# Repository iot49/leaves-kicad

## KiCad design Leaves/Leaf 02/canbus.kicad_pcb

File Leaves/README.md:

# Leaves

## Leaf 01: FRAM, Gyro, Canbus, BMI270, Hall Current Sensors (ADS1015), Supply Voltage Sense

* FRAM
* Canbus
* INA3221     
  * BUG: IN1-, IN2- not connected - Vsense1, Vsense2 always zero
  * Channel3 works (Vbus = Vin = ~12V nominal)
* ADS1015
* BMI270
* TMP1075     
  * BUG: address conflict with ADS1015 (TMP1075 removed)

## Leaf 02: FRAM, Gyro, Canbus, BMI270, Hall Current Sensors (ADS1015), Voltage Sense, Temperature

* Leaf 01 fixed
  * TMP1075 at 0x49
  * INA3221: IN1-=IN1+, IN2-=IN2+

## Leaf 03: Hall Current Sensors (ADS1015), Voltage Sense, Temperature, Buses (???)

* Leaf 01/02 with different buses
  * no Canbus, Gyro

* 3 (or 4) Hall Current Sensors
* Switched 12V (2 simultaneously should suffice)
  * Fan
  * Battery low voltage disconnect Victron BP12/24-100
  * House to Chassis charger
* 3 voltage inputs
  * Ignition
  * Chassis battery voltage
  * BP12 disconnect. Note: Power Leaf from an unswitched source, e.g. chassis

Connectors:  (Hammond 1593VBK accommodates up to 93mm)
* 4 Hall         40   mm
* 1 fan          10   mm
* Tool free: 8   33   mm  (3.5mm, 16-24 gauge)
  * 2 for Power, Ground
  * 3 Voltage inputs
  * 2 Switched outputs (1 shared with fan?)
  * 1 extra?
* Extra grove connectors other side? 3/5V?
* Buses fro Trume, Xantrex, RVC, Linbus?

Maybe:

* Bus for
  * Truma water heater
  * Xantex freedom 2000
  * Dometic fridge (Linbus)

## Leaf 04: Cooling Fan Controller, 12V switched out

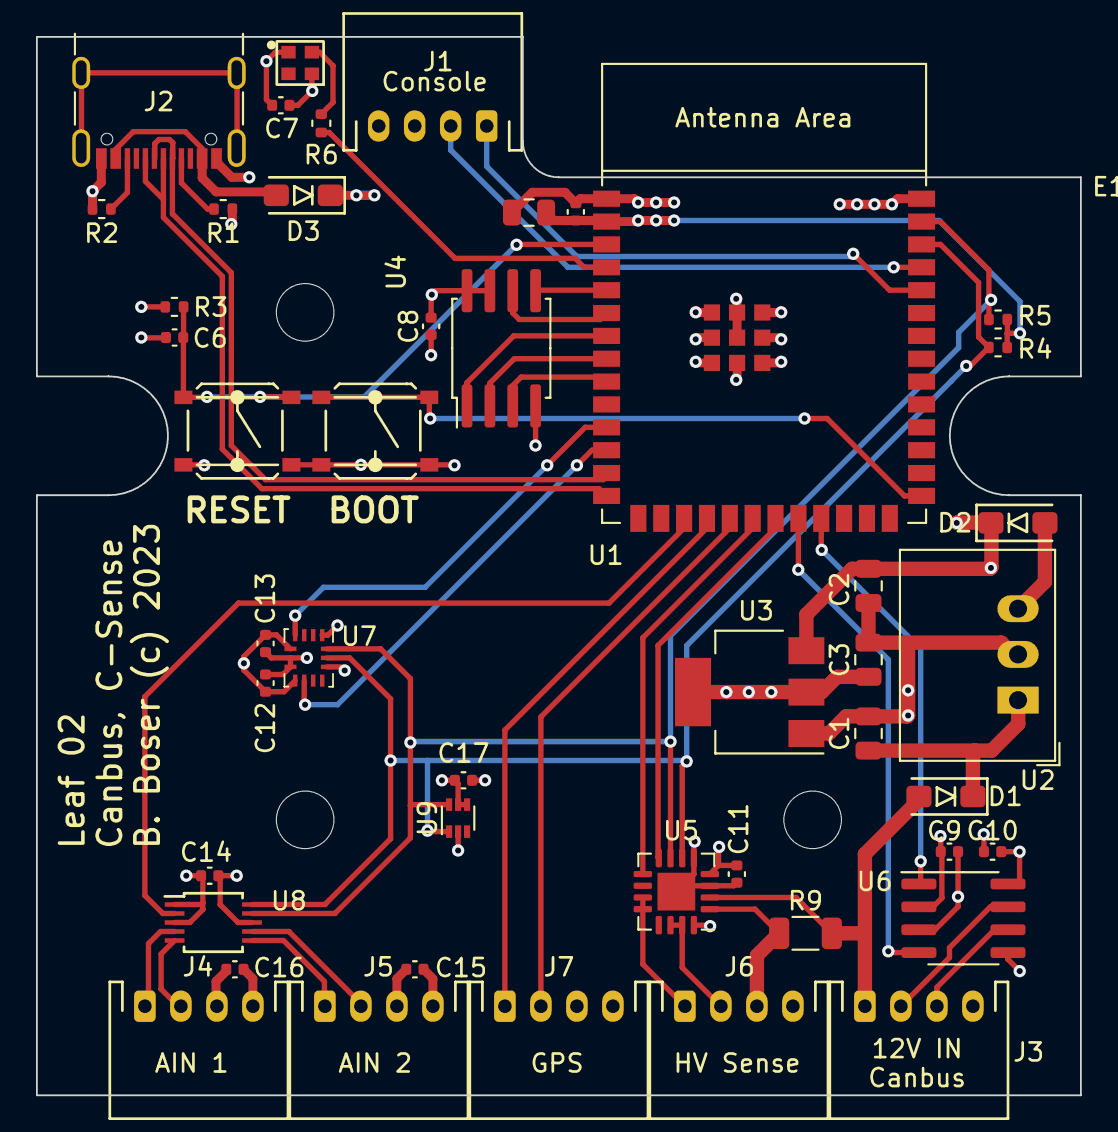
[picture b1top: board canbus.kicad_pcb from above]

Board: 4 copper layers, 58.0 x 58.8 mm, 47 parts (0 on the bottom side), 42 nets.

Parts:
C1, C2, C3, C4: 10u; C_0805_2012Metric
C5, C7, C8, C9, C10, C11, C12, C13, C14, C15, C16, C17: 100n; C_0402_1005Metric
C6: 1uF; C_0402_1005Metric
D1, D2, D3: 1N5819WS; SOD-123
E1: 1593k; Hammond_1593K_WROOM
J1: Console; JST_PH_S4B-PH-K_1x04_P2.00mm_Horizontal
J2: USB_C_Receptacle_USB2.0; USB_C_Receptacle_GCT_USB4105-xx-A_16P_TopMnt_Horizontal
J3: Power; JST_PH_S4B-PH-K_1x04_P2.00mm_Horizontal
J4: AIN1; JST_PH_S4B-PH-K_1x04_P2.00mm_Horizontal
J5: AIN2; JST_PH_S4B-PH-K_1x04_P2.00mm_Horizontal
J6: HV Sense; JST_PH_S4B-PH-K_1x04_P2.00mm_Horizontal
J7: GPS; JST_PH_S4B-PH-K_1x04_P2.00mm_Horizontal
LED1: SK6805; SK6805-EK20
R1, R2, R4, R5: 5.1k; R_0402_1005Metric
R3: 10k; R_0402_1005Metric
R6: 510; R_0402_1005Metric
R9: 150m; R_1206_3216Metric
SW1: BOOT; TS-1187A
SW2: RESET; TS-1187A
U1: ESP32-S3-WROOM-1
U2: R-78E5.0-1.0; Converter_DCDC_RECOM_R-78E-0.5_THT
U3: AMS1117-3.3; SOT-223-3_TabPin2
U4: MB85RS2MT; SOP-8_MP85RS2
U5: INA3221; Texas_RGV_S-PVQFN-N16_EP2.1x2.1mm
U6: MCP2562-E-SN; SOIC-8_3.9x4.9mm_P1.27mm
U7: BMI270; Bosch_LGA-14_3x2.5mm_P0.5mm
U8: ADS1015IDGS; TSSOP-10_3x3mm_P0.5mm
U9: TMP1075NDRLR; SOT-563

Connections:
+3.3V: C3.1, C4.1, C5.1, C7.1, C8.1, C10.1, C11.1, C12.1, C13.1, C14.1, C17.1, J7.3, LED1.4 (VDD), R3.1, R4.1, R5.2, U1.2 (3V3), U3.2 (VO), U4.7 (~HOLD), U4.8 (VDD), U5.4 (VS), U5.16 (VPU), U6.5 (Vio), U7.5 (VDDIO), U7.8 (VDD), U7.12 (CSB), U8.8 (VDD), U9.4 (A0), U9.5 (V+)
+5V: C2.1, C9.1, C15.1, C16.1, D2.1 (K), D3.1 (K), J1.3, J4.3, J5.3, U3.3 (VI), U6.3 (VDD)
+12V: C1.1, D1.1 (K), U2.1 (IN)
/VUSB: D3.2 (A), J2.A4 (VBUS), J2.A9 (VBUS), J2.B4 (VBUS), J2.B9 (VBUS)
/Vreg: D2.2 (A), U2.3 (OUT)
/io/AIN1+: J4.1, U8.4 (AIN0)
/io/AIN1-: J4.2, U8.5 (AIN1)
/io/AIN2+: J5.1, U8.6 (AIN2)
/io/AIN2-: J5.2, U8.7 (AIN3)
/io/CAN_H: J3.2, U6.7 (CANH)
/io/CAN_L: J3.3, U6.6 (CANL)
/io/Vout: J6.3, R9.1, U5.1 (IN-3)
/io/Vsense1: J6.1, U5.11 (IN-1), U5.12 (IN+1)
/io/Vsense2: J6.2, U5.14 (IN-2), U5.15 (IN+2)
ADC_ALERT: U1.17 (GPIO9/TOUCH9/ADC1_CH8/FSPIHD/SUBSPIHD), U8.2 (ALERT/RDY)
BOOT: SW1.1, U1.27 (GPIO0/BOOT)
CAN_RXD: U1.22 (GPIO14/TOUCH14/ADC2_CH3/FSPIWP/FSPIDQS/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), U6.4 (RXD)
CAN_TXD: U1.23 (GPIO21), U6.1 (TXD)
CS_CRITICAL: U1.20 (GPIO12/TOUCH12/ADC2_CH1/FSPICLK/FSPIIO6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), U5.9 (CRITICAL)
CS_WARNING: U1.21 (GPIO13/TOUCH13/ADC2_CH2/FSPIQ/FSPIIO7/S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), U5.8 (WARNING)
D+: J2.A6 (D+), J2.B6 (D+), U1.14 (GPIO20/U1CTS/ADC2_CH9/CLK_OUT1/USB_D+)
D-: J2.A7 (D-), J2.B7 (D-), U1.13 (GPIO19/U1RTS/ADC2_CH8/CLK_OUT2/USB_D-)
FRAM_CS: U1.7 (GPIO7/TOUCH7/ADC1_CH6), U4.1 (~CS)
FRAM_MISO: U1.8 (GPIO15/U0RTS/ADC2_CH4/XTAL_32K_P), U4.2 (SO)
FRAM_MOSI: U1.5 (GPIO5/TOUCH5/ADC1_CH4), U4.5 (SI)
FRAM_SCK: U1.6 (GPIO6/TOUCH6/ADC1_CH5), U4.6 (SCK)
FRAM_WP: U1.9 (GPIO16/U0CTS/ADC2_CH5/XTAL_32K_N), U4.3 (~WP)
GND: C1.2, C2.2, C3.2, C4.2, C5.2, C6.2, C7.2, C8.2, C9.2, C10.2, C11.2, C12.2, C13.2, C14.2, C15.2, C16.2, C17.2, J1.4, J2.A1 (GND), J2.A12 (GND), J2.B1 (GND), J2.B12 (GND), J3.4, J4.4, J5.4, J6.4, J7.4, LED1.2 (VSS), R1.2, R2.2, SW1.2, SW2.2, U1.1 (GND), U1.40 (GND), U1.41 (GND), U2.2 (GND), U3.1 (GND), U4.4 (GND), U5.3 (GND), U5.5 (A0), U5.17 (EP), U6.2 (VSS), U6.8 (STBY), U7.1 (SDO), U7.6 (GNDIO), U7.7 (GND), U8.1 (ADDR), U8.3 (GND), U9.2 (GND)
GPS_RX: J7.1, U1.18 (GPIO10/TOUCH10/ADC1_CH9/FSPICS0/FSPIIO4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)
GPS_TX: J7.2, U1.19 (GPIO11/TOUCH11/ADC2_CH0/FSPID/FSPIIO5/S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)
IMU_INT1: U1.11 (GPIO18/U1RXD/ADC2_CH7/CLK_OUT3), U7.4 (INT1)
IMU_INT2: U1.12 (GPIO8/TOUCH8/ADC1_CH7/SUBSPICS1), U7.9 (INT2)
LED: R6.1, U1.4 (GPIO4/TOUCH4/ADC1_CH3)
unnamed: J2.A5 (CC1), R1.1
unnamed: J2.B5 (CC2), R2.1
unnamed: LED1.3 (DIN), R6.2
RESET: C6.1, R3.2, SW2.1, U1.3 (EN)
SCL: R4.2, U1.38 (GPIO2/TOUCH2/ADC1_CH1), U5.6 (SCL), U7.13 (SCx), U8.10 (SCL), U9.1 (SCL)
SDA: R5.1, U1.39 (GPIO1/TOUCH1/ADC1_CH0), U5.7 (SDA), U7.14 (SDx), U8.9 (SDA), U9.6 (SDA)
U0RXD: J1.1, U1.36 (U0RXD/GPIO44/CLK_OUT2)
U0TXD: J1.2, U1.37 (U0TXD/GPIO43/CLK_OUT1)
Vin: D1.2 (A), J3.1, R9.2, U5.2 (IN+3)

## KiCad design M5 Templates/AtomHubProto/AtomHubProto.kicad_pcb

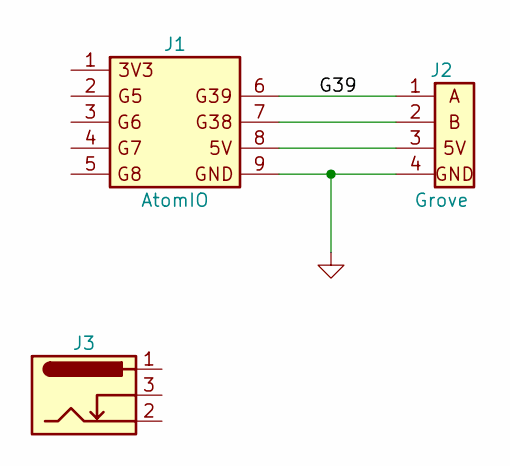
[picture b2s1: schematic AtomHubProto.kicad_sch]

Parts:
J1: AtomIO
J2: Grove
J3: Barrel_Jack_Switch; PowerJack

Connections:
/G39: J1.6, J2.1
GND: J1.9, J2.4 (GND)
unnamed: J1.7, J2.2
unnamed: J1.8, J2.3 (5V)

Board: 2 copper layers, 3 parts (0 on the bottom side), 4 nets, no tracks yet.

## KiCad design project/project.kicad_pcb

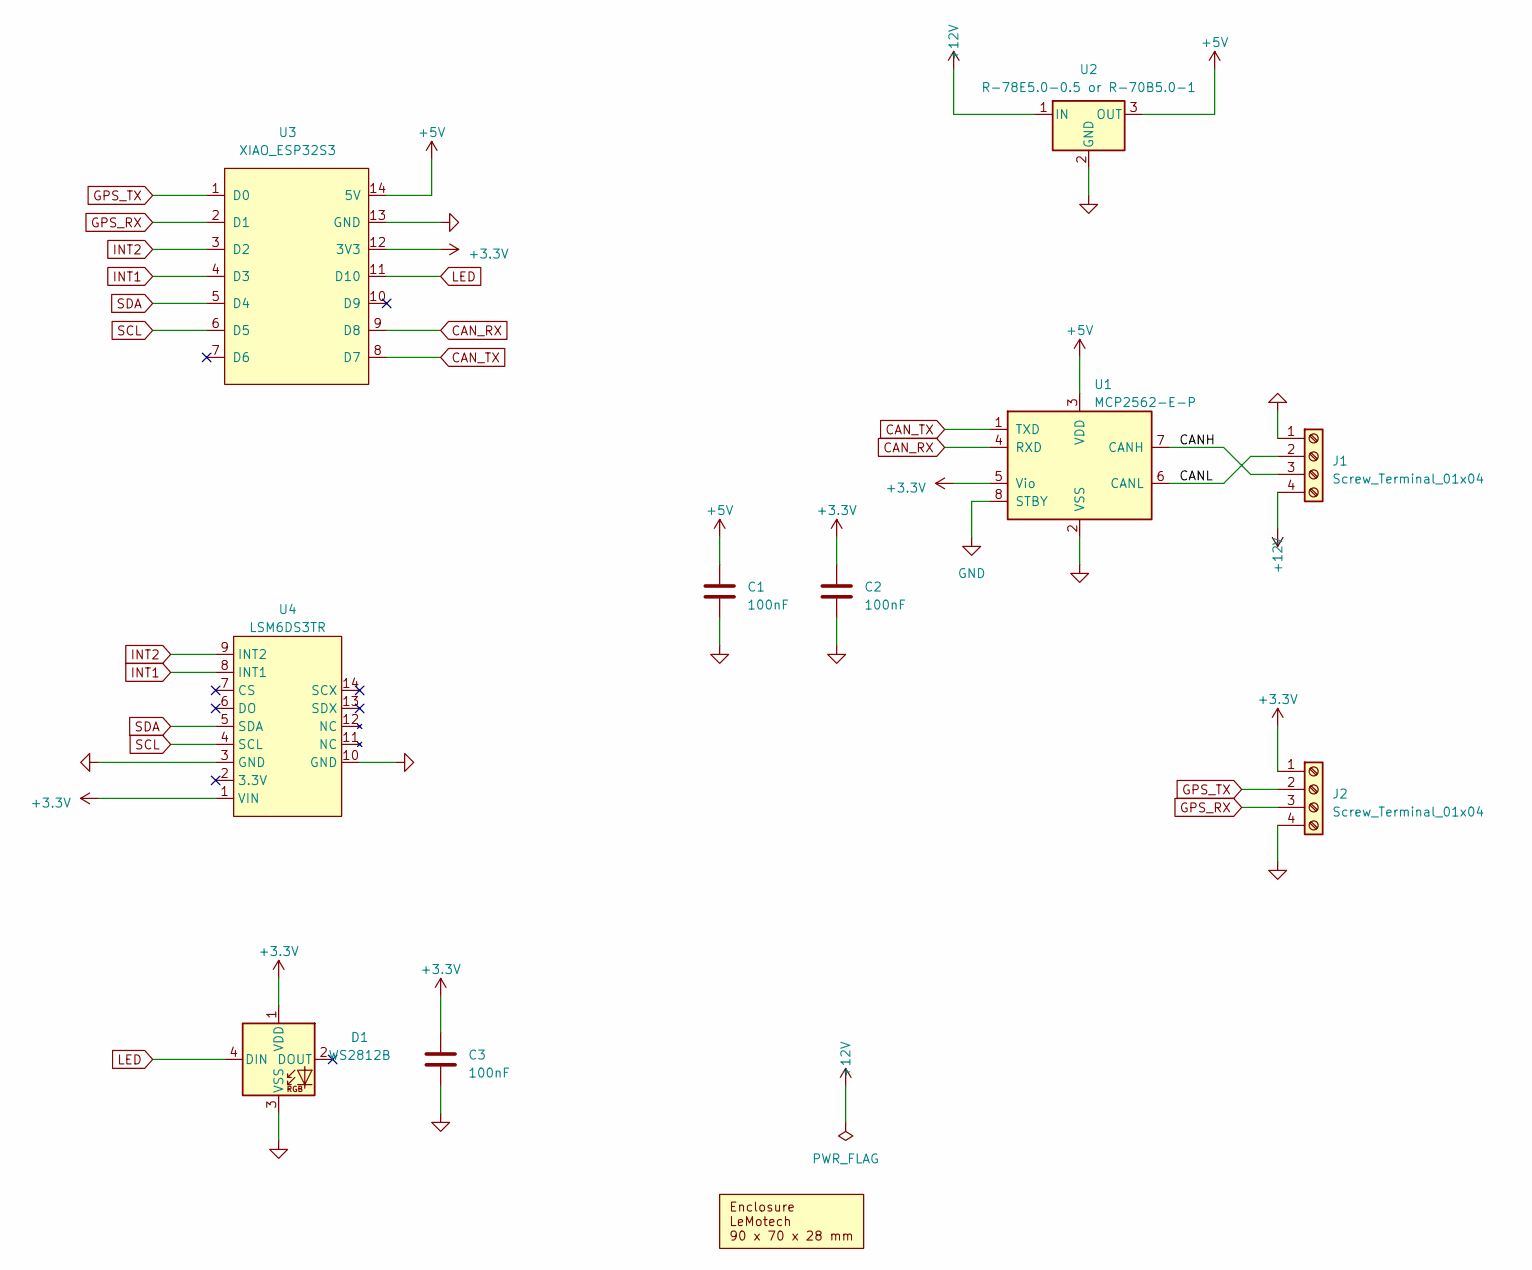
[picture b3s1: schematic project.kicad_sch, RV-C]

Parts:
C1, C2, C3: 100nF; C_Rect_L7.0mm_W3.5mm_P5.00mm
D1: WS2812B; LED_WS2812B_PLCC4_5.0x5.0mm_P3.2mm; Digikey 1568-COM-16347TR-ND
J1, J2: Screw_Terminal_01x04; PhoenixContact_MC_1,5_4-G-3.81_1x04_P3.81mm_Horizontal
U1: MCP2562-E-P; DIP-8_W7.62mm; Digikey MCP2562FD-E/P-ND
U2: R-78E5.0-0.5 or R-70B5.0-1; Converter_DCDC_RECOM_R-78E-0.5_THT; Digikey 945-1648-5-ND
U3: XIAO_ESP32S3; XIAO_DIL
U4: LSM6DS3TR; LSM6DS3TR_breakout
X1: Enclosure_Lemotech_90_70_antenna

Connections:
+3.3V: C2.1, C3.1, D1.1 (VDD), J2.1, U1.5 (Vio), U3.12 (3V3), U4.1 (VIN)
+5V: C1.1, U1.3 (VDD), U2.3 (OUT), U3.14 (5V)
+12V: J1.4, U2.1 (IN)
/CANH: J1.3, U1.7 (CANH)
/CANL: J1.2, U1.6 (CANL)
CAN_RX: U1.4 (RXD), U3.9 (D8)
CAN_TX: U1.1 (TXD), U3.8 (D7)
GND: C1.2, C2.2, C3.2, D1.3 (VSS), J1.1, J2.4, U1.2 (VSS), U1.8 (STBY), U2.2 (GND), U3.13 (GND), U4.3 (GND), U4.10 (GND)
GPS_RX: J2.3, U3.2 (D1)
GPS_TX: J2.2, U3.1 (D0)
INT1: U3.4 (D3), U4.8 (INT1)
INT2: U3.3 (D2), U4.9 (INT2)
LED: D1.4 (DIN), U3.11 (D10)
SCL: U3.6 (D5), U4.4 (SCL)
SDA: U3.5 (D4), U4.5 (SDA)

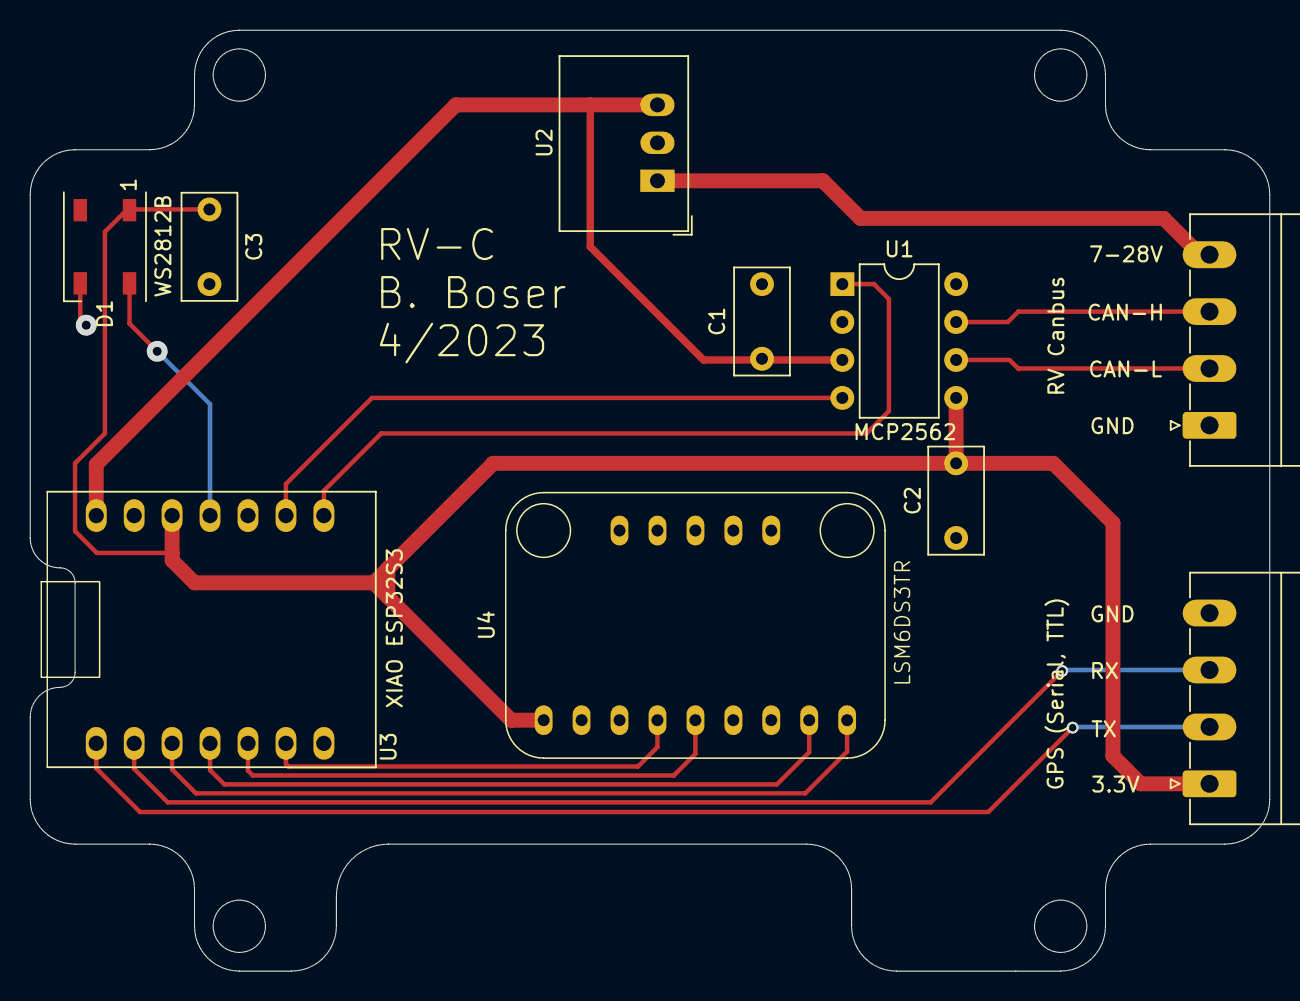
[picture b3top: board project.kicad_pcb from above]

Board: 2 copper layers, 83.0 x 63.0 mm, 11 parts (0 on the bottom side), 15 nets.

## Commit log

2023-05-03 initial
2023-08-05 add AtomHubProto pcb layout
2023-12-18 V 0.1

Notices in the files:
Leaves/Leaf 02/canbus.kicad_pcb:
B. Boser (c) 2023
